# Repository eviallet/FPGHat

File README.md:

# FPGHat
 iCE40 FPGA & STM32 MCU project

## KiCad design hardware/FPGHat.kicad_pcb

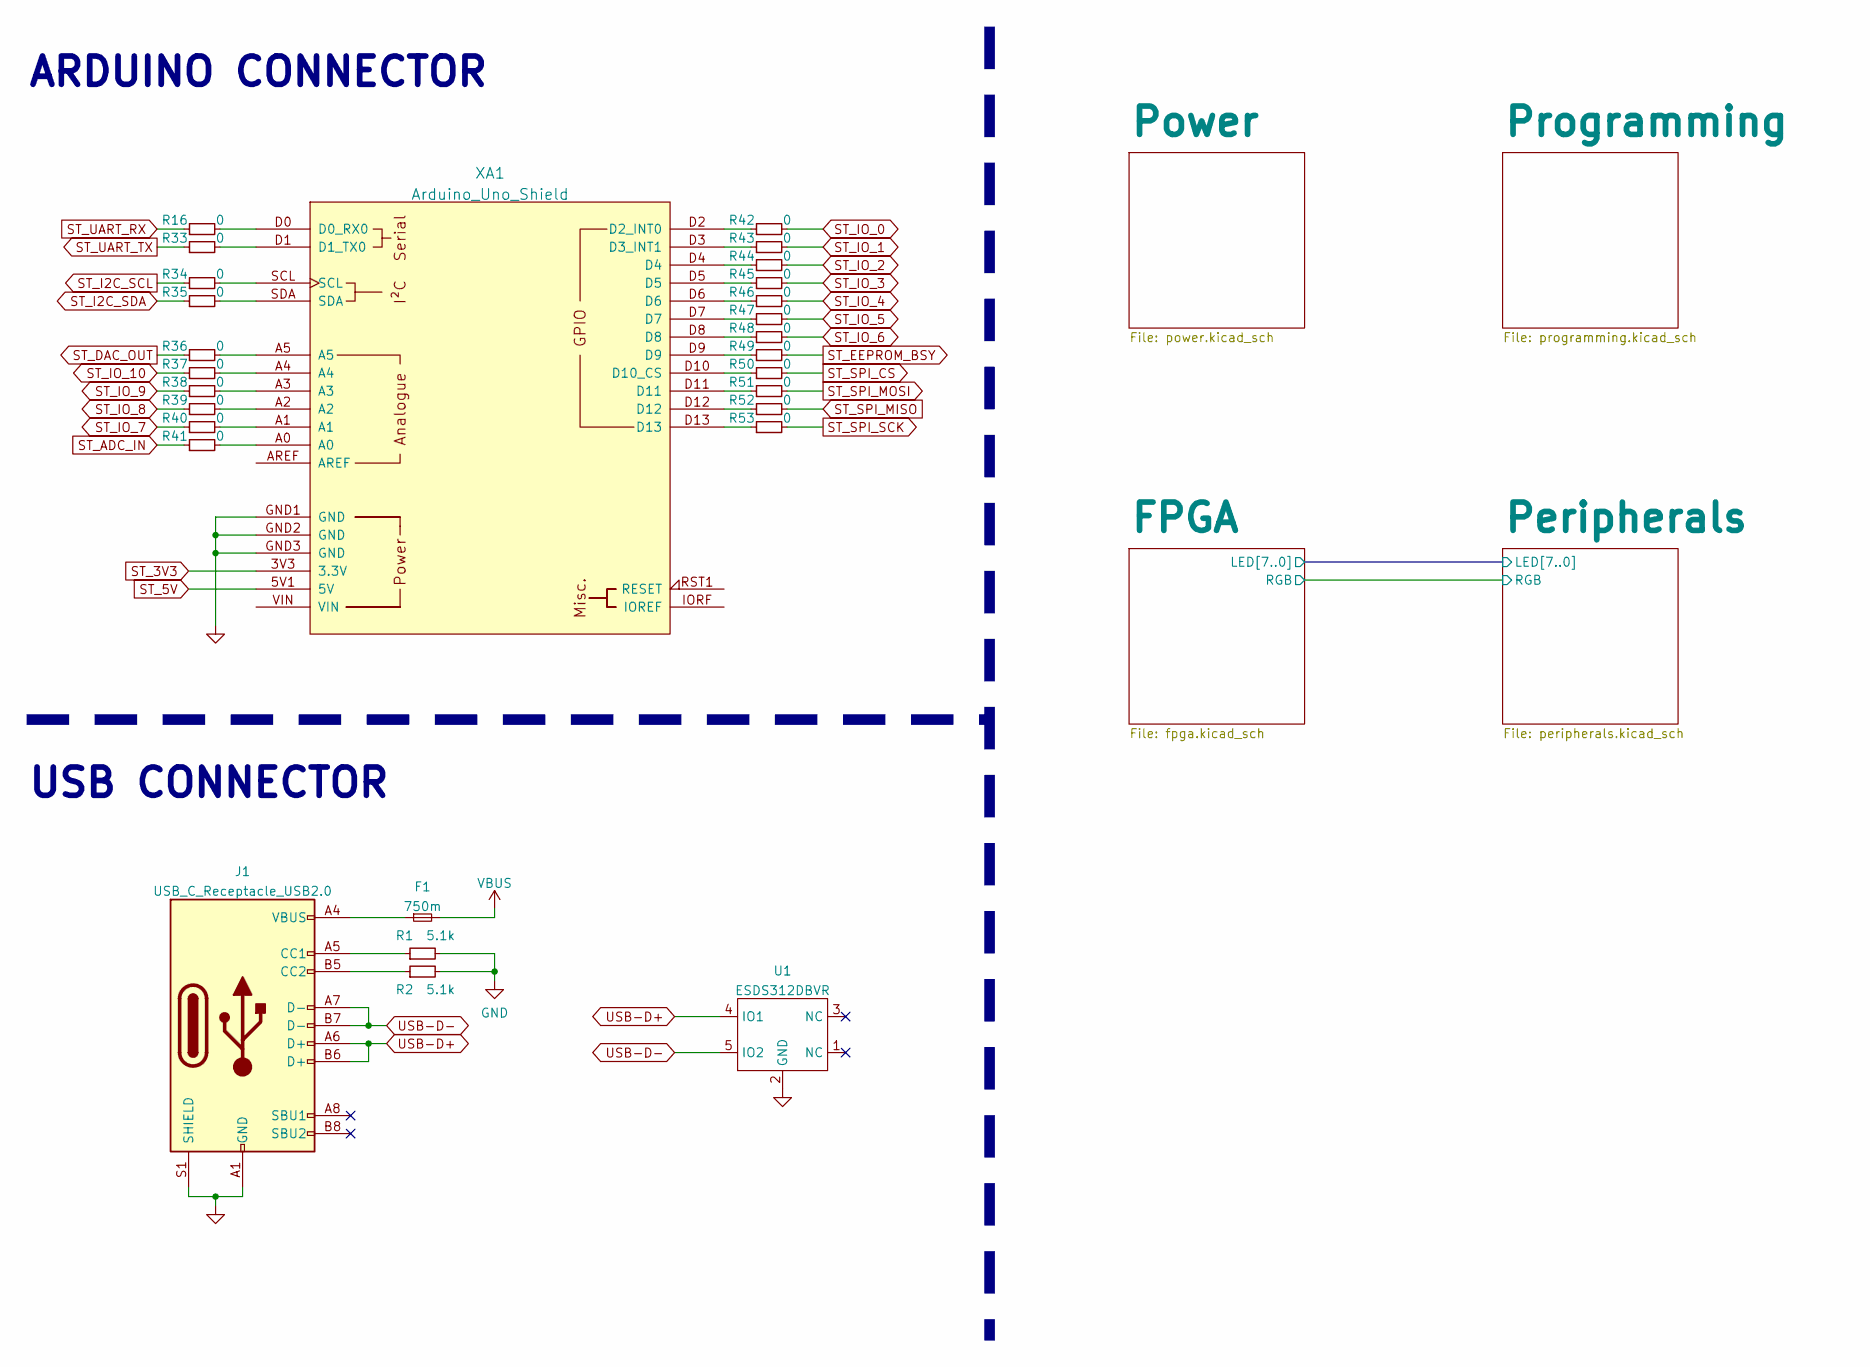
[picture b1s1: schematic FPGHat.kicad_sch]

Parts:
F1: 750m; Fuse_0603_1608Metric
J1: USB_C_Receptacle_USB2.0; USB_C_Molex_216990-0002
R1, R2: 5.1k; R_0402_1005Metric
R16, R33, R34, R35, R36, R37, R38, R39, R40, R41, R42, R43, R44, R45, R46, R47, R48, R49, R50, R51, R52, R53: 0; R_0402_1005Metric
U1: ESDS312DBVR; SOT-23-5
XA1: Arduino_Uno_Shield; Arduino_Uno_Custom_Hat

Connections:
FPGA_I2C_SCL: R34.1; also elsewhere on the board
FPGA_I2C_SDA: R35.1; also elsewhere on the board
GND: J1.A1 (GND), J1.A12 (GND), J1.B1 (GND), J1.B12 (GND), J1.S1 (SHIELD), R1.2, R2.2, U1.2 (GND), XA1.GND1 (GND), XA1.GND2 (GND), XA1.GND3 (GND); also elsewhere on the board
unnamed: F1.1, J1.A4 (VBUS), J1.A9 (VBUS), J1.B4 (VBUS), J1.B9 (VBUS)
unnamed: J1.A5 (CC1), R1.1
unnamed: J1.B5 (CC2), R2.1
unnamed: R16.2, XA1.D0 (D0_RX0)
unnamed: R33.2, XA1.D1 (D1_TX0)
unnamed: R34.2, XA1.SCL
unnamed: R35.2, XA1.SDA
unnamed: R36.2, XA1.A5
unnamed: R37.2, XA1.A4
unnamed: R38.2, XA1.A3
unnamed: R39.2, XA1.A2
unnamed: R40.2, XA1.A1
unnamed: R41.2, XA1.A0
unnamed: R42.1, XA1.D2 (D2_INT0)
unnamed: R43.1, XA1.D3 (D3_INT1)
unnamed: R44.1, XA1.D4
unnamed: R45.1, XA1.D5
unnamed: R46.1, XA1.D6
unnamed: R47.1, XA1.D7
unnamed: R48.1, XA1.D8
unnamed: R49.1, XA1.D9
unnamed: R50.1, XA1.D10 (D10_CS)
unnamed: R51.1, XA1.D11
unnamed: R52.1, XA1.D12
unnamed: R53.1, XA1.D13
ST_3V3: XA1.3V3 (3.3V); also elsewhere on the board
ST_5V: XA1.5V1 (5V); also elsewhere on the board
ST_ADC_IN: R41.1; also elsewhere on the board
ST_DAC_OUT: R36.1; also elsewhere on the board
ST_EEPROM_BSY: R49.2; also elsewhere on the board
ST_IO_0: R42.2
ST_IO_1: R43.2; also elsewhere on the board
ST_IO_3: R45.2; also elsewhere on the board
ST_IO_4: R46.2; also elsewhere on the board
ST_IO_5: R47.2; also elsewhere on the board
ST_IO_6: R48.2; also elsewhere on the board
ST_IO_7: R40.1; also elsewhere on the board
ST_IO_8: R39.1
ST_IO_9: R38.1
ST_IO_10: R37.1
ST_SPI_CS: R50.2; also elsewhere on the board
ST_SPI_MISO: R52.2; also elsewhere on the board
ST_SPI_MOSI: R51.2; also elsewhere on the board
ST_SPI_SCK: R53.2; also elsewhere on the board
ST_UART_RX: R16.1; also elsewhere on the board
ST_UART_TX: R33.1; also elsewhere on the board
USB-D+: J1.A6 (D+), J1.B6 (D+), U1.4 (IO1); also elsewhere on the board
USB-D-: J1.A7 (D-), J1.B7 (D-), U1.5 (IO2); also elsewhere on the board
VBUS: F1.2; also elsewhere on the board

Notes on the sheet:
USB CONNECTOR
ARDUINO CONNECTOR

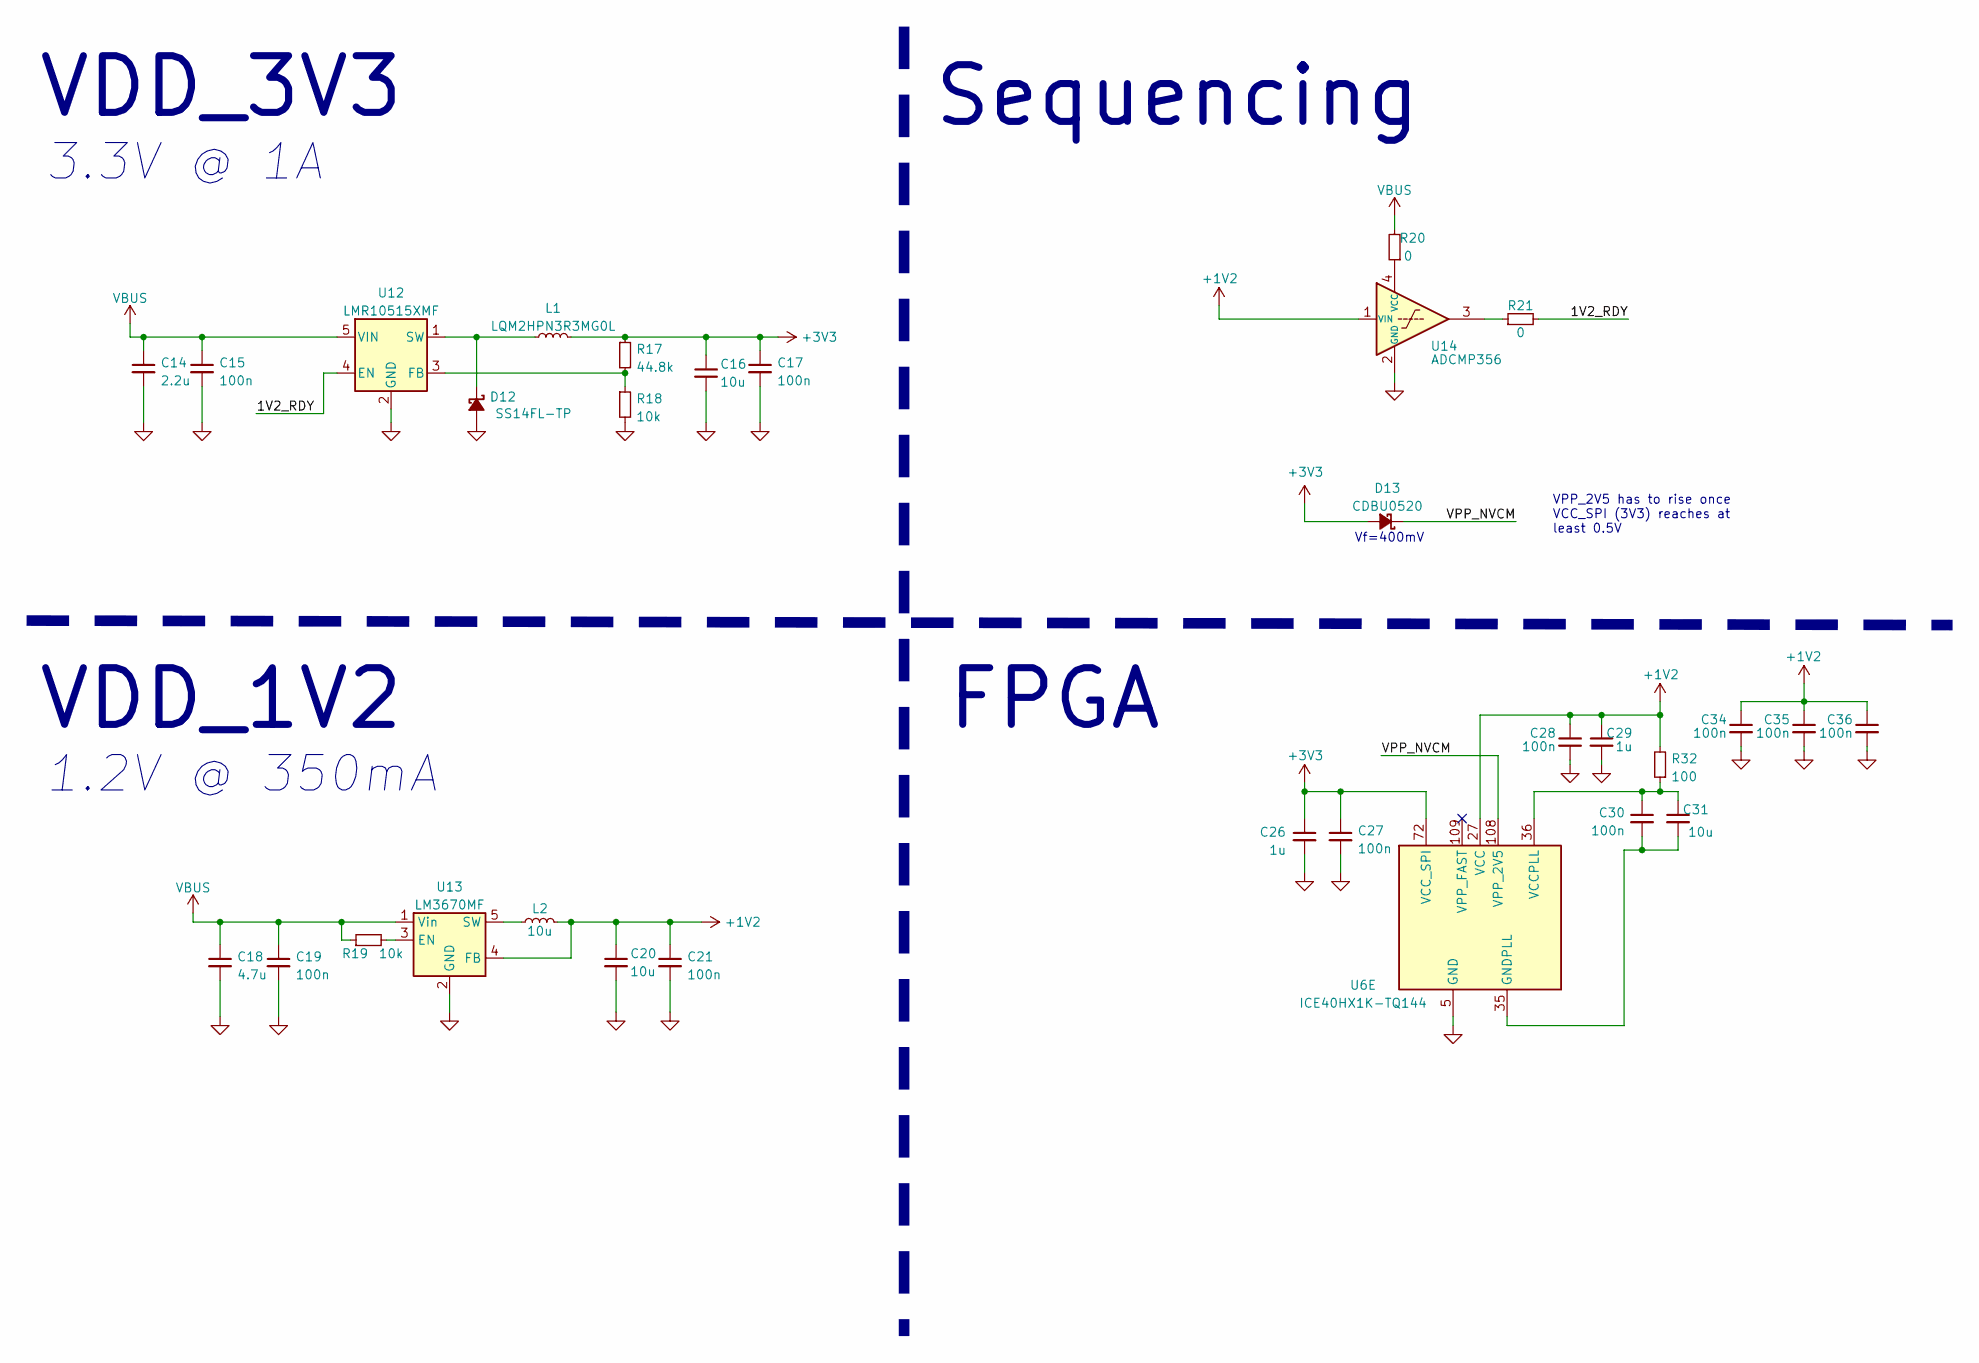
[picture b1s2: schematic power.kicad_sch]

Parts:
C14: 2.2u; C_1210_3225Metric
C15, C17, C19, C21, C27, C28, C30, C34, C35, C36: 100n; C_0402_1005Metric
C16, C20: 10u; C_1812_4532Metric
C18: 4.7u; C_1210_3225Metric
C26, C29: 1u; C_0603_1608Metric
C31: 10u; C_0603_1608Metric
D12: SS14FL-TP; DO-221AC-2
D13: CDBU0520; D_0603_1608Metric
L1: LQM2HPN3R3MG0L; L_1008_2520Metric
L2: 10u; L_Coilcraft_D01608C
R17: 44.8k; R_0402_1005Metric; Tolerance 0.1%
R18: 10k; R_0402_1005Metric; Tolerance 0.1%
R19: 10k; R_0402_1005Metric
R20, R21: 0; R_0402_1005Metric
R32: 100; R_0402_1005Metric
U6: ICE40HX1K-TQ144; TQFP-144_20x20mm_P0.5mm
U12: LMR10515XMF; SOT-23-5
U13: LM3670MF; TSOT-23-5
U14: ADCMP356; Analog_KS-4

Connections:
+1V2: C20.1, C21.1, C28.1, C29.1, C34.1, C35.1, C36.1, L2.2, R32.2, U6.27 (VCC), U6.51 (VCC), U6.92 (VCC), U6.111 (VCC), U13.4 (FB), U14.1 (VIN)
+3V3: C16.1, C17.1, C26.1, C27.1, D13.2 (A), L1.2, R17.1, U6.72 (VCC_SPI); also elsewhere on the board
/Power/1V2_RDY: R21.2, U12.4 (EN)
/Power/VPP_NVCM: D13.1 (K), U6.108 (VPP_2V5)
GND: C14.2, C15.2, C16.2, C17.2, C18.2, C19.2, C20.2, C21.2, C26.2, C27.2, C28.2, C29.2, C34.2, C35.2, C36.2, D12.2 (A), R18.2, U6.5 (GND), U6.13 (GND), U6.14 (GND), U6.59 (GND), U6.69 (GND), U6.86 (GND), U6.103 (GND), U6.132 (GND), U6.140 (GND), U12.2 (GND), U13.2 (GND), U14.2 (GND); also elsewhere on the board
unnamed: C30.1, C31.1, R32.1, U6.36 (VCCPLL)
unnamed: C30.2, C31.2, U6.35 (GNDPLL)
unnamed: D12.1 (K), L1.1, U12.1 (SW)
unnamed: L2.1, U13.5 (SW)
unnamed: R17.2, R18.1, U12.3 (FB)
unnamed: R19.2, U13.3 (EN)
unnamed: R20.1, U14.4 (VCC)
unnamed: R21.1, U14.3
VBUS: C14.1, C15.1, C18.1, C19.1, R19.1, R20.2, U12.5 (VIN), U13.1 (Vin); also elsewhere on the board

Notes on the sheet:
Sequencing
VDD_1V2
VDD_3V3
Vf=400mV
FPGA
1.2V @ 350mA
VPP_2V5 has to rise once VCC_SPI (3V3) reaches at least 0.5V
3.3V @ 1A

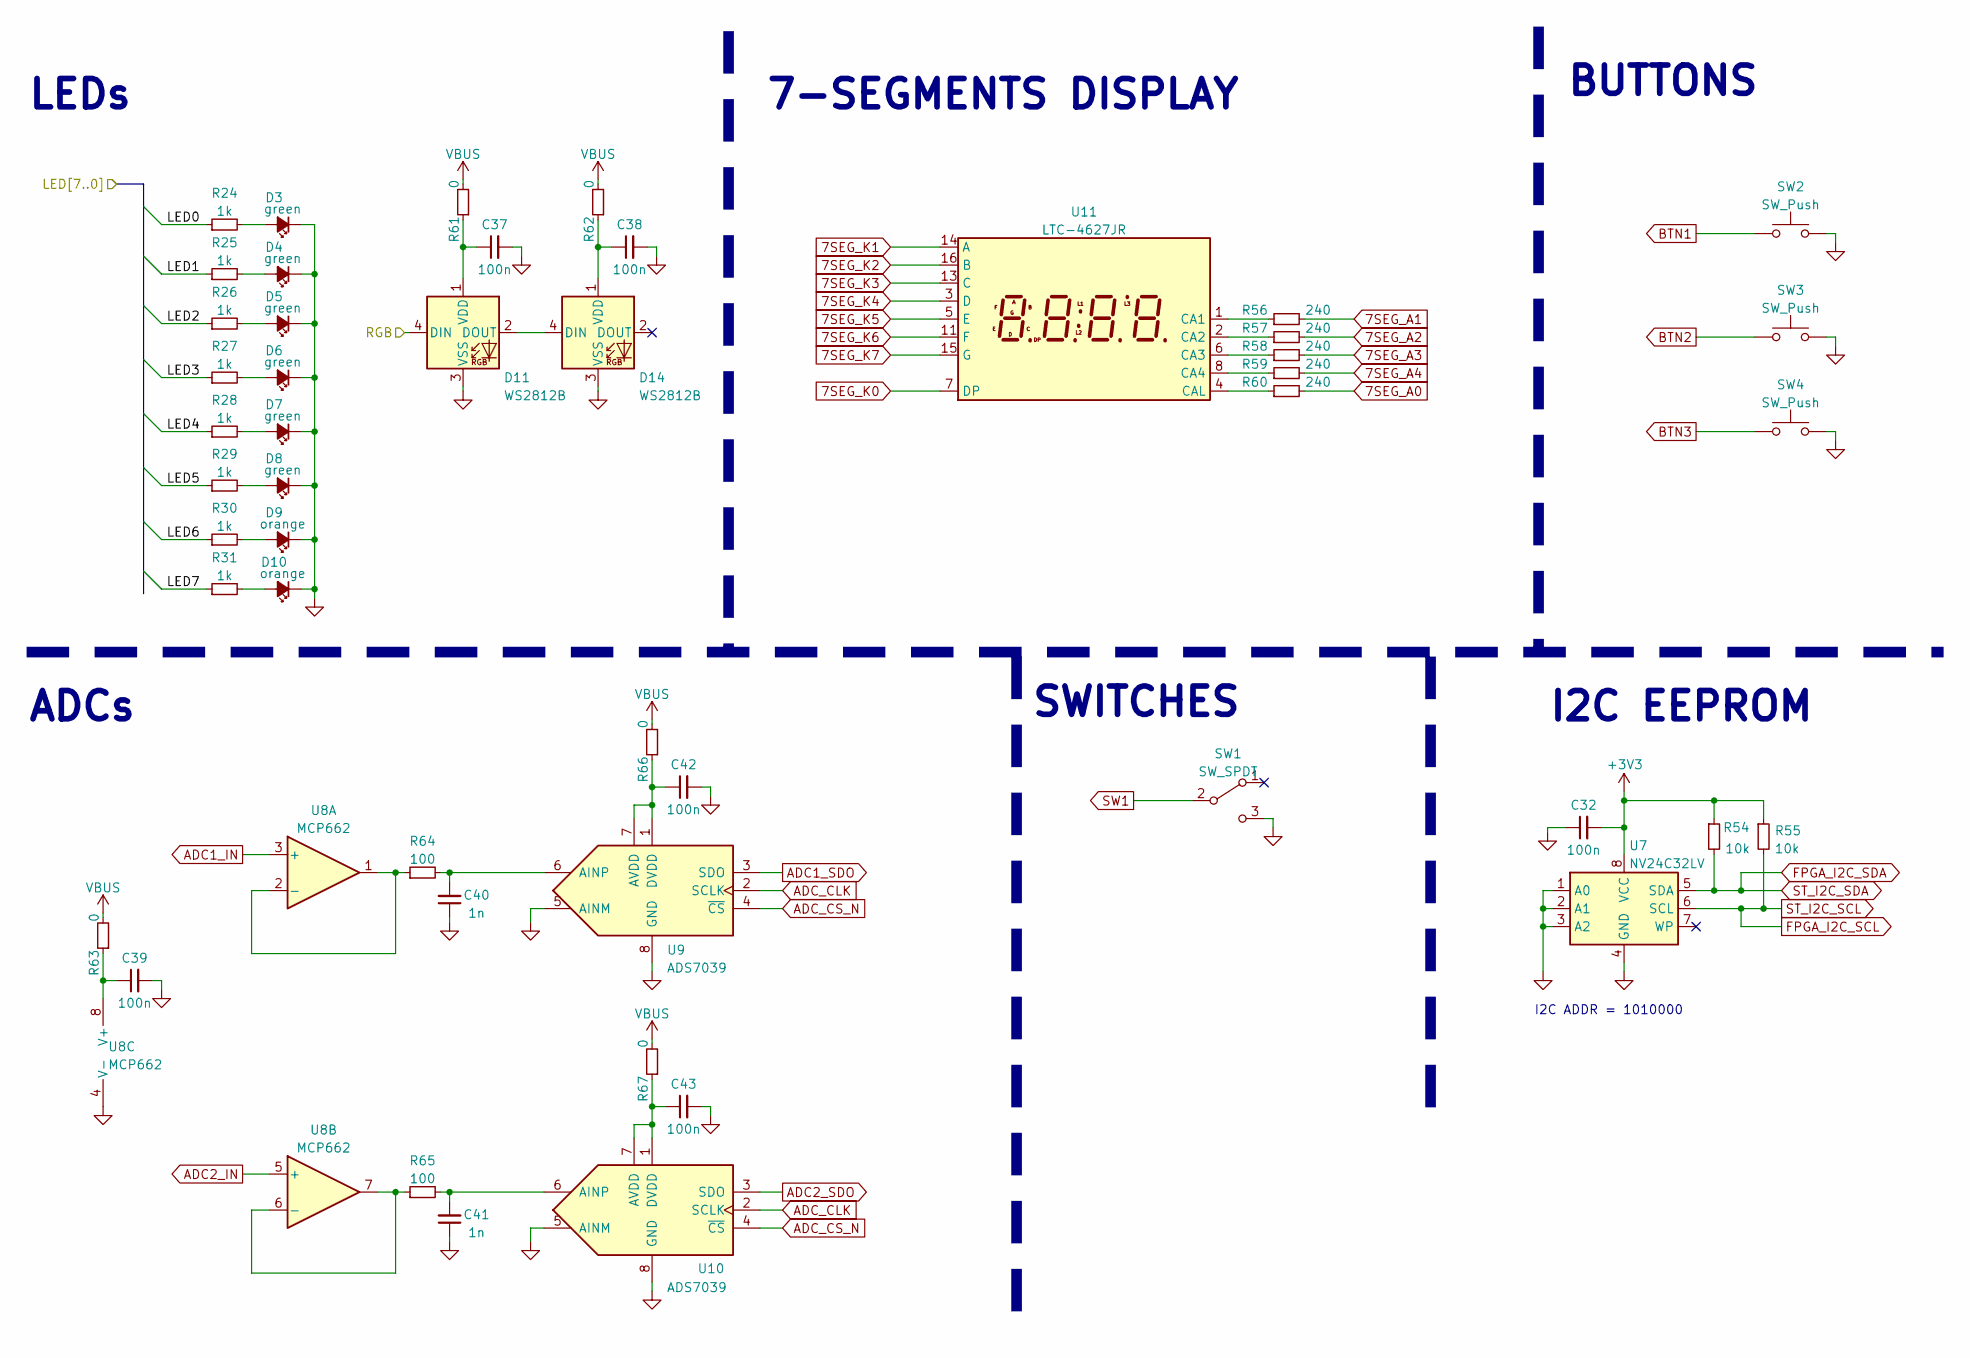
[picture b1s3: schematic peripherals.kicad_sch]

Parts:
C32, C37, C38, C39, C42, C43: 100n; C_0402_1005Metric
C40, C41: 1n; C_0402_1005Metric
D3, D4, D5, D6, D7, D8: green; LED_0603_1608Metric
D9, D10: orange; LED_0603_1608Metric
D11, D14: WS2812B; LED_WS2812B_PLCC4_5.0x5.0mm_P3.2mm
R24, R25, R26, R27, R28, R29, R30, R31: 1k; R_0402_1005Metric
R54, R55: 10k; R_0402_1005Metric
R56, R57, R58, R59, R60: 240; R_0402_1005Metric
R61, R62, R63, R66, R67: 0; R_0402_1005Metric
R64, R65: 100; R_0402_1005Metric
SW1: SW_SPDT; SW_SPDT_CK-JS102011SAQN
SW2, SW3, SW4: SW_Push; SW_Push_SPST_NO_Alps_SKRK
U7: NV24C32LV; SOIC-8_3.9x4.9mm_P1.27mm
U8: MCP662; SOIC-8_3.9x4.9mm_P1.27mm
U9, U10: ADS7039; VSSOP-8_2.3x2mm_P0.5mm
U11: LTC-4627JR; LTC-4627Jx

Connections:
7SEG_A0: R60.2; also elsewhere on the board
7SEG_A1: R56.2; also elsewhere on the board
7SEG_A2: R57.2; also elsewhere on the board
7SEG_A3: R58.2; also elsewhere on the board
7SEG_A4: R59.2; also elsewhere on the board
7SEG_K0: U11.7 (DP); also elsewhere on the board
7SEG_K1: U11.14 (A); also elsewhere on the board
7SEG_K2: U11.16 (B); also elsewhere on the board
7SEG_K3: U11.13 (C); also elsewhere on the board
7SEG_K4: U11.3 (D); also elsewhere on the board
7SEG_K5: U11.5 (E); also elsewhere on the board
7SEG_K6: U11.11 (F); also elsewhere on the board
7SEG_K7: U11.15 (G); also elsewhere on the board
+3V3: C32.2, R54.1, R55.1, U7.8 (VCC); also elsewhere on the board
/FPGA/LED0: R24.1; also elsewhere on the board
/FPGA/LED1: R25.1; also elsewhere on the board
/FPGA/LED2: R26.1; also elsewhere on the board
/FPGA/LED3: R27.1; also elsewhere on the board
/FPGA/LED4: R28.1; also elsewhere on the board
/FPGA/LED5: R29.1; also elsewhere on the board
/FPGA/LED6: R30.1; also elsewhere on the board
/FPGA/LED7: R31.1; also elsewhere on the board
/FPGA/RGB: D11.4 (DIN); also elsewhere on the board
ADC1_IN: U8.3 (+); also elsewhere on the board
ADC1_SDO: U9.3 (SDO); also elsewhere on the board
ADC2_IN: U8.5 (+); also elsewhere on the board
ADC2_SDO: U10.3 (SDO); also elsewhere on the board
ADC_CLK: U9.2 (SCLK), U10.2 (SCLK); also elsewhere on the board
ADC_CS_N: U9.4 (~CS), U10.4 (~CS); also elsewhere on the board
BTN2: SW3.1; also elsewhere on the board
BTN3: SW4.1; also elsewhere on the board
FPGA_I2C_SCL: R55.2, U7.6 (SCL); also elsewhere on the board
FPGA_I2C_SDA: R54.2, U7.5 (SDA); also elsewhere on the board
GND: C32.1, C37.2, C38.2, C39.2, C40.1, C41.1, C42.2, C43.2, D3.1 (K), D4.1 (K), D5.1 (K), D6.1 (K), D7.1 (K), D8.1 (K), D9.1 (K), D10.1 (K), D11.3 (VSS), D14.3 (VSS), SW1.3 (C), SW2.2, SW3.2, SW4.2, U7.1 (A0), U7.2 (A1), U7.3 (A2), U7.4 (GND), U8.4 (V-), U9.5 (AINM), U9.8 (GND), U10.5 (AINM), U10.8 (GND); also elsewhere on the board
unnamed: C37.1, D11.1 (VDD), R61.1
unnamed: C38.1, D14.1 (VDD), R62.1
unnamed: C39.1, R63.1, U8.8 (V+)
unnamed: C40.2, R64.2, U9.6 (AINP)
unnamed: C41.2, R65.2, U10.6 (AINP)
unnamed: C42.1, R66.1, U9.1 (DVDD), U9.7 (AVDD)
unnamed: C43.1, R67.1, U10.1 (DVDD), U10.7 (AVDD)
unnamed: D3.2 (A), R24.2
unnamed: D4.2 (A), R25.2
unnamed: D5.2 (A), R26.2
unnamed: D6.2 (A), R27.2
unnamed: D7.2 (A), R28.2
unnamed: D8.2 (A), R29.2
unnamed: D9.2 (A), R30.2
unnamed: D10.2 (A), R31.2
unnamed: D11.2 (DOUT), D14.4 (DIN)
unnamed: R56.1, U11.1 (CA1)
unnamed: R57.1, U11.2 (CA2)
unnamed: R58.1, U11.6 (CA3)
unnamed: R59.1, U11.8 (CA4)
unnamed: R60.1, U11.4 (CAL)
unnamed: R64.1, U8.1, U8.2 (-)
unnamed: R65.1, U8.6 (-), U8.7
SW1: SW1.2 (B); also elsewhere on the board
VBUS: R61.2, R62.2, R63.2, R66.2, R67.2; also elsewhere on the board

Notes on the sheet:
BUTTONS
ADCs
I2C ADDR = 1010000
LEDs
I2C EEPROM
7-SEGMENTS DISPLAY
SWITCHES

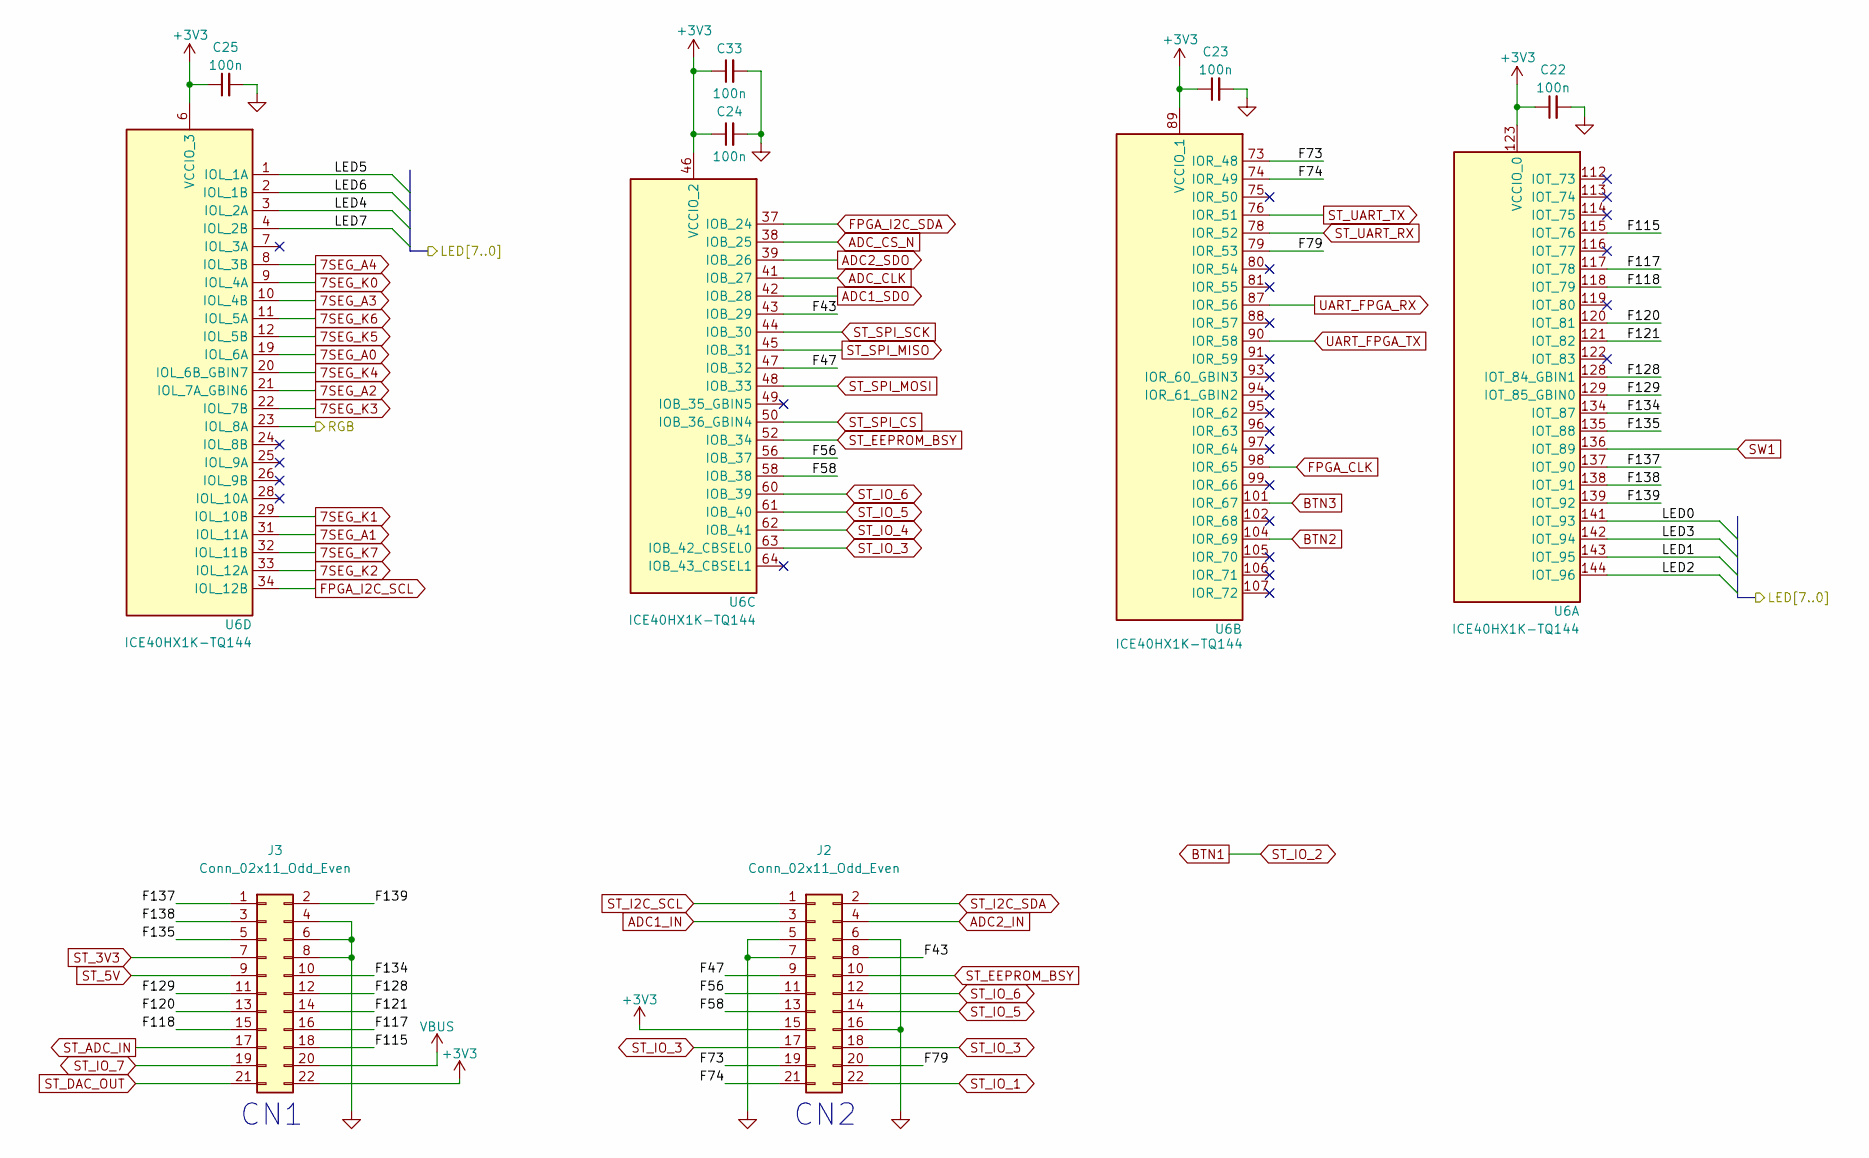
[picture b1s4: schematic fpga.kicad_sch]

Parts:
C22, C23, C24, C25, C33: 100n; C_0402_1005Metric
J2, J3: Conn_02x11_Odd_Even; PinHeader_2x11_P2.54mm_Vertical_SMD
U6: ICE40HX1K-TQ144; TQFP-144_20x20mm_P0.5mm

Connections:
7SEG_A0: U6.19 (IOL_6A); also elsewhere on the board
7SEG_A1: U6.31 (IOL_11A); also elsewhere on the board
7SEG_A2: U6.21 (IOL_7A_GBIN6); also elsewhere on the board
7SEG_A3: U6.10 (IOL_4B); also elsewhere on the board
7SEG_A4: U6.8 (IOL_3B); also elsewhere on the board
7SEG_K0: U6.9 (IOL_4A); also elsewhere on the board
7SEG_K1: U6.29 (IOL_10B); also elsewhere on the board
7SEG_K2: U6.33 (IOL_12A); also elsewhere on the board
7SEG_K3: U6.22 (IOL_7B); also elsewhere on the board
7SEG_K4: U6.20 (IOL_6B_GBIN7); also elsewhere on the board
7SEG_K5: U6.12 (IOL_5B); also elsewhere on the board
7SEG_K6: U6.11 (IOL_5A); also elsewhere on the board
7SEG_K7: U6.32 (IOL_11B); also elsewhere on the board
+3V3: C22.1, C23.1, C24.1, C25.1, C33.1, J2.15, J3.22, U6.6 (VCCIO_3), U6.30 (VCCIO_3), U6.46 (VCCIO_2), U6.57 (VCCIO_2), U6.89 (VCCIO_1), U6.100 (VCCIO_1), U6.123 (VCCIO_0), U6.133 (VCCIO_0); also elsewhere on the board
/FPGA/F43: J2.8, U6.43 (IOB_29)
/FPGA/F47: J2.9, U6.47 (IOB_32)
/FPGA/F56: J2.11, U6.56 (IOB_37)
/FPGA/F58: J2.13, U6.58 (IOB_38)
/FPGA/F73: J2.19, U6.73 (IOR_48)
/FPGA/F74: J2.21, U6.74 (IOR_49)
/FPGA/F79: J2.20, U6.79 (IOR_53)
/FPGA/F115: J3.18, U6.115 (IOT_76)
/FPGA/F117: J3.16, U6.117 (IOT_78)
/FPGA/F118: J3.15, U6.118 (IOT_79)
/FPGA/F120: J3.13, U6.120 (IOT_81)
/FPGA/F121: J3.14, U6.121 (IOT_82)
/FPGA/F128: J3.12, U6.128 (IOT_84_GBIN1)
/FPGA/F129: J3.11, U6.129 (IOT_85_GBIN0)
/FPGA/F134: J3.10, U6.134 (IOT_87)
/FPGA/F135: J3.5, U6.135 (IOT_88)
/FPGA/F137: J3.1, U6.137 (IOT_90)
/FPGA/F138: J3.3, U6.138 (IOT_91)
/FPGA/F139: J3.2, U6.139 (IOT_92)
/FPGA/LED0: U6.141 (IOT_93); also elsewhere on the board
/FPGA/LED1: U6.143 (IOT_95); also elsewhere on the board
/FPGA/LED2: U6.144 (IOT_96); also elsewhere on the board
/FPGA/LED3: U6.142 (IOT_94); also elsewhere on the board
/FPGA/LED4: U6.3 (IOL_2A); also elsewhere on the board
/FPGA/LED5: U6.1 (IOL_1A); also elsewhere on the board
/FPGA/LED6: U6.2 (IOL_1B); also elsewhere on the board
/FPGA/LED7: U6.4 (IOL_2B); also elsewhere on the board
/FPGA/RGB: U6.23 (IOL_8A); also elsewhere on the board
ADC1_IN: J2.3; also elsewhere on the board
ADC1_SDO: U6.42 (IOB_28); also elsewhere on the board
ADC2_IN: J2.4; also elsewhere on the board
ADC2_SDO: U6.39 (IOB_26); also elsewhere on the board
ADC_CLK: U6.41 (IOB_27); also elsewhere on the board
ADC_CS_N: U6.38 (IOB_25); also elsewhere on the board
BTN2: U6.104 (IOR_69); also elsewhere on the board
BTN3: U6.101 (IOR_67); also elsewhere on the board
FPGA_CLK: U6.98 (IOR_65); also elsewhere on the board
FPGA_I2C_SCL: J2.1, U6.34 (IOL_12B); also elsewhere on the board
FPGA_I2C_SDA: J2.2, U6.37 (IOB_24); also elsewhere on the board
GND: C22.2, C23.2, C24.2, C25.2, C33.2, J2.5, J2.6, J2.7, J2.16, J3.4, J3.6, J3.8; also elsewhere on the board
ST_3V3: J3.7; also elsewhere on the board
ST_5V: J3.9; also elsewhere on the board
ST_ADC_IN: J3.17; also elsewhere on the board
ST_DAC_OUT: J3.21; also elsewhere on the board
ST_EEPROM_BSY: J2.10, U6.52 (IOB_34); also elsewhere on the board
ST_IO_1: J2.22; also elsewhere on the board
ST_IO_3: J2.17, J2.18, U6.63 (IOB_42_CBSEL0); also elsewhere on the board
ST_IO_4: U6.62 (IOB_41); also elsewhere on the board
ST_IO_5: J2.14, U6.61 (IOB_40); also elsewhere on the board
ST_IO_6: J2.12, U6.60 (IOB_39); also elsewhere on the board
ST_IO_7: J3.19; also elsewhere on the board
ST_SPI_CS: U6.50 (IOB_36_GBIN4); also elsewhere on the board
ST_SPI_MISO: U6.45 (IOB_31); also elsewhere on the board
ST_SPI_MOSI: U6.48 (IOB_33); also elsewhere on the board
ST_SPI_SCK: U6.44 (IOB_30); also elsewhere on the board
ST_UART_RX: U6.78 (IOR_52); also elsewhere on the board
ST_UART_TX: U6.76 (IOR_51); also elsewhere on the board
SW1: U6.136 (IOT_89); also elsewhere on the board
UART_FPGA_RX: U6.87 (IOR_56); also elsewhere on the board
UART_FPGA_TX: U6.90 (IOR_58); also elsewhere on the board
VBUS: J3.20; also elsewhere on the board

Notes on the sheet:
CN1
CN2

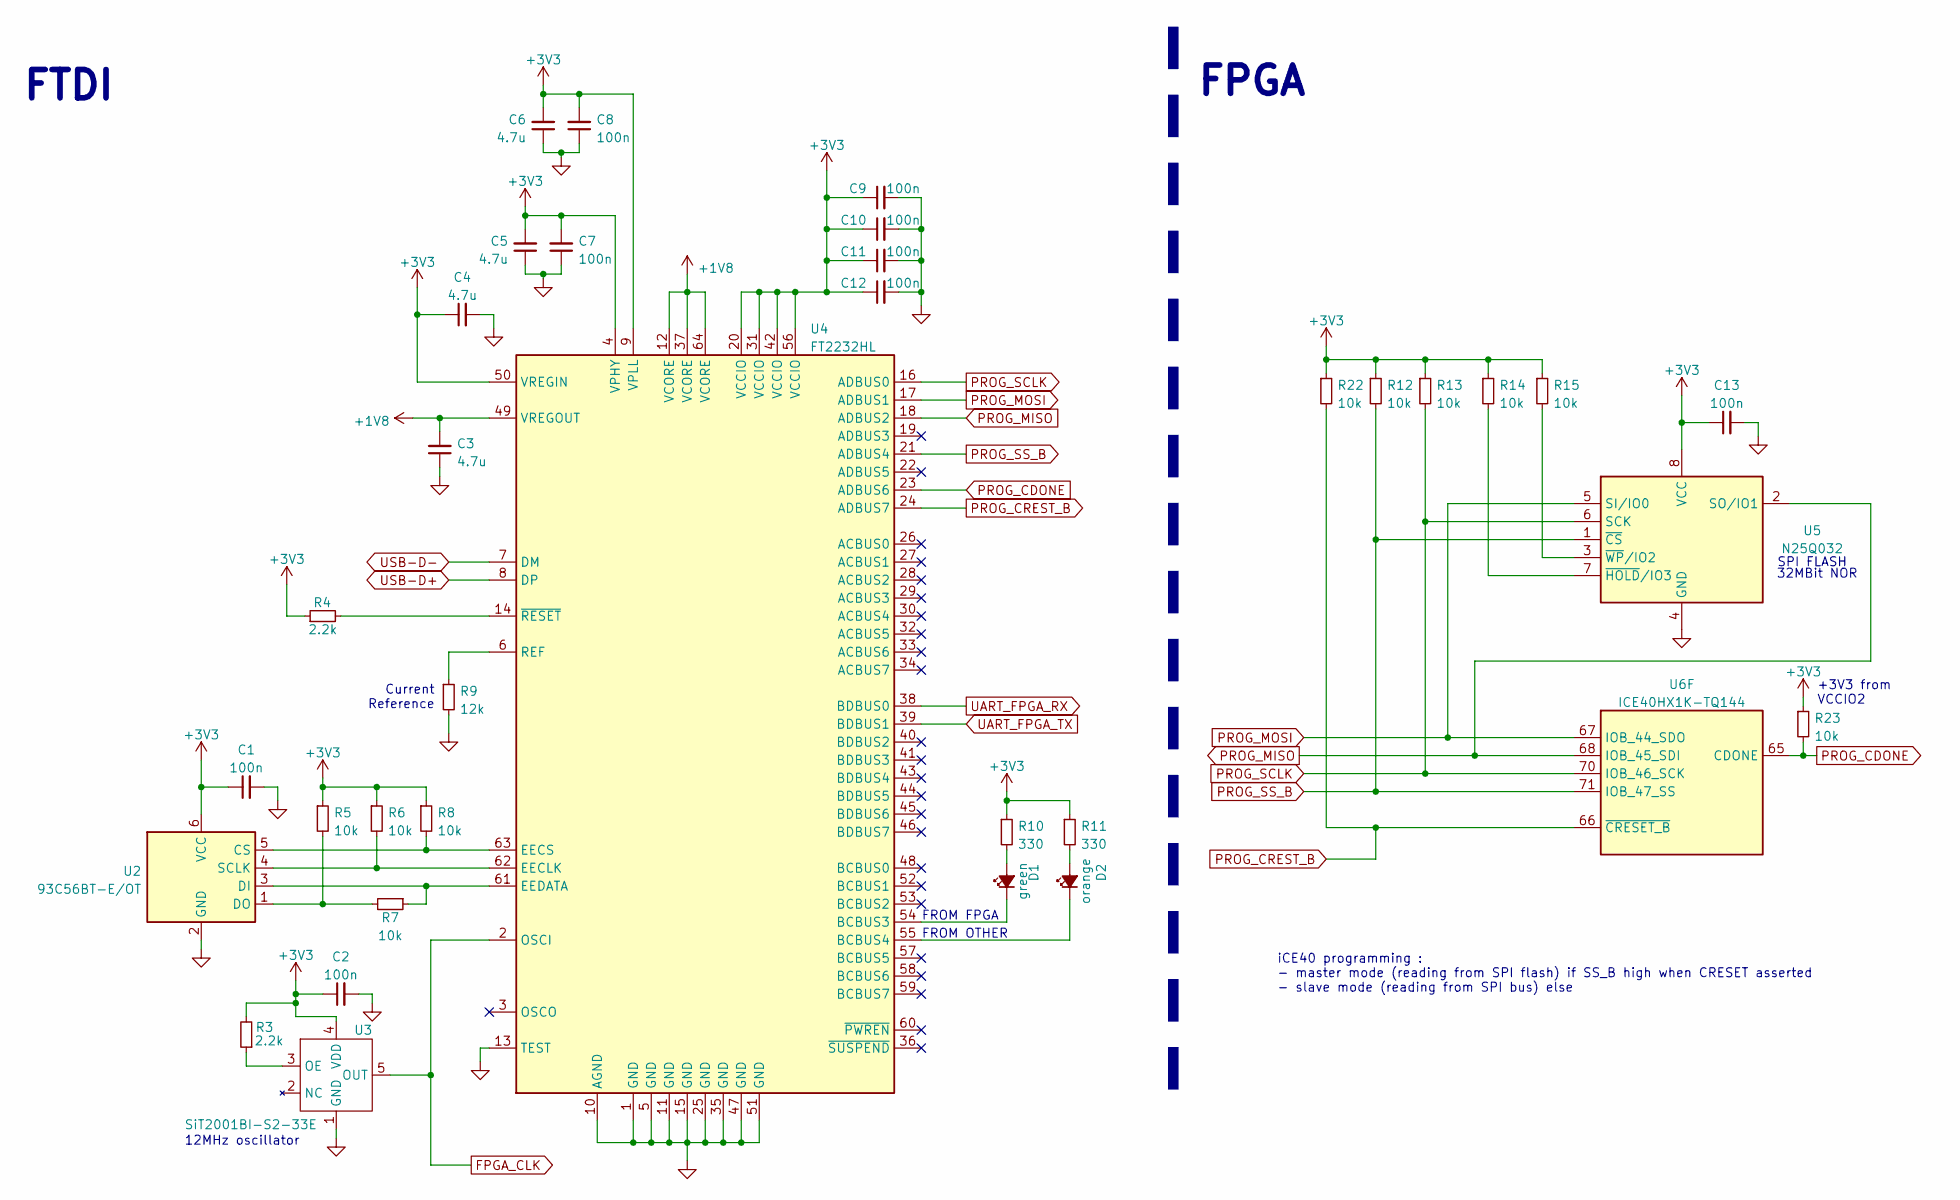
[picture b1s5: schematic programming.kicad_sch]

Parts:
C1, C2, C7, C8, C9, C10, C11, C12, C13: 100n; C_0402_1005Metric
C3, C4, C5, C6: 4.7u; C_0603_1608Metric
D1: green; LED_0603_1608Metric
D2: orange; LED_0603_1608Metric
R3, R4: 2.2k; R_0402_1005Metric
R5, R6, R7, R8, R12, R13, R14, R15, R22, R23: 10k; R_0402_1005Metric
R9: 12k; R_0402_1005Metric; Tolerance 0.1%
R10, R11: 330; R_0402_1005Metric
U2: 93C56BT-E/OT; SOT-23-6
U3: SiT2001BI-S2-33E; SOT-23-5
U4: FT2232HL; LQFP-64_10x10mm_P0.5mm
U5: N25Q032; SOP2-8
U6: ICE40HX1K-TQ144; TQFP-144_20x20mm_P0.5mm

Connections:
+1V8: C3.2, U4.12 (VCORE), U4.37 (VCORE), U4.49 (VREGOUT), U4.64 (VCORE)
+3V3: C1.1, C2.1, C4.1, C5.2, C6.2, C7.2, C8.2, C9.1, C10.1, C11.1, C12.1, C13.1, R3.2, R4.1, R5.1, R6.1, R8.1, R10.1, R11.1, R12.1, R13.1, R14.1, R15.1, R22.1, R23.1, U2.6 (VCC), U3.4 (VDD), U4.4 (VPHY), U4.9 (VPLL), U4.20 (VCCIO), U4.31 (VCCIO), U4.42 (VCCIO), U4.50 (VREGIN), U4.56 (VCCIO), U5.8 (VCC); also elsewhere on the board
FPGA_CLK: U3.5 (OUT), U4.2 (OSCI); also elsewhere on the board
GND: C1.2, C2.2, C3.1, C4.2, C5.1, C6.1, C7.1, C8.1, C9.2, C10.2, C11.2, C12.2, C13.2, R9.2, U2.2 (GND), U3.1 (GND), U4.1 (GND), U4.5 (GND), U4.10 (AGND), U4.11 (GND), U4.13 (TEST), U4.15 (GND), U4.25 (GND), U4.35 (GND), U4.47 (GND), U4.51 (GND), U5.4 (GND); also elsewhere on the board
unnamed: D1.1 (K), U4.54 (BCBUS3)
unnamed: D1.2 (A), R10.2
unnamed: D2.1 (K), U4.55 (BCBUS4)
unnamed: D2.2 (A), R11.2
unnamed: R3.1, U3.3 (OE)
unnamed: R4.2, U4.14 (~RESET)
unnamed: R5.2, R7.2, U2.1 (DO)
unnamed: R6.2, U2.4 (SCLK), U4.62 (EECLK)
unnamed: R7.1, U2.3 (DI), U4.61 (EEDATA)
unnamed: R8.2, U2.5 (CS), U4.63 (EECS)
unnamed: R9.1, U4.6 (REF)
unnamed: R14.2, U5.7 (~HOLD/IO3)
unnamed: R15.2, U5.3 (~WP/IO2)
PROG_CDONE: R23.2, U4.23 (ADBUS6), U6.65 (CDONE)
PROG_CREST_B: R22.2, U4.24 (ADBUS7), U6.66 (~CRESET_B)
PROG_MISO: U4.18 (ADBUS2), U5.2 (SO/IO1), U6.68 (IOB_45_SDI)
PROG_MOSI: U4.17 (ADBUS1), U5.5 (SI/IO0), U6.67 (IOB_44_SDO)
PROG_SCLK: R13.2, U4.16 (ADBUS0), U5.6 (SCK), U6.70 (IOB_46_SCK)
PROG_SS_B: R12.2, U4.21 (ADBUS4), U5.1 (~CS), U6.71 (IOB_47_SS)
UART_FPGA_RX: U4.38 (BDBUS0); also elsewhere on the board
UART_FPGA_TX: U4.39 (BDBUS1); also elsewhere on the board
USB-D+: U4.8 (DP); also elsewhere on the board
USB-D-: U4.7 (DM); also elsewhere on the board

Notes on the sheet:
Current Reference
32MBit NOR
FTDI
FROM FPGA
12MHz oscillator
FROM OTHER
FPGA
SPI FLASH
iCE40 programming : - master mode (reading from SPI flash) if SS_B high when CRESET asserted - slave mode (reading from SPI bus) else
+3V3 from VCCIO2

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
